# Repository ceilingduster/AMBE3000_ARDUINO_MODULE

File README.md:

# AMBE3000 Arduino Module in KiCad 8
A PCB containing a DVSI AMBE-3000R (or AMBE-3003) Vocoders for use with WebSDRs/Audio transcoding.

This board is based on the design by George Smart, M1GEO and Chris Smart, G8OCV.

The DVSI AMBE parts can be purchased in low volume from the [DVSI Inc. Hardware Product Pricing](https://www.dvsinc.com/products/price.shtml) page. You will need to create a purchase order to buy from DVSI.

# Assembly

The design schematic include details for [JLCPCB](https://jlcpcb.com/) assembly, who assembled mine. You'll likely have to reflow the DVSI AMBE-3000R part yourself, which I did with a PCB reflow hotplate, but you can do any way you wish.

Each schematic component has a [JLCPCB Parts](https://jlcpcb.com/parts)/[LCSC](https://www.lcsc.com/) part number (Cxxxxxx), which can be exported to the BoM using the extra field "LCSC".

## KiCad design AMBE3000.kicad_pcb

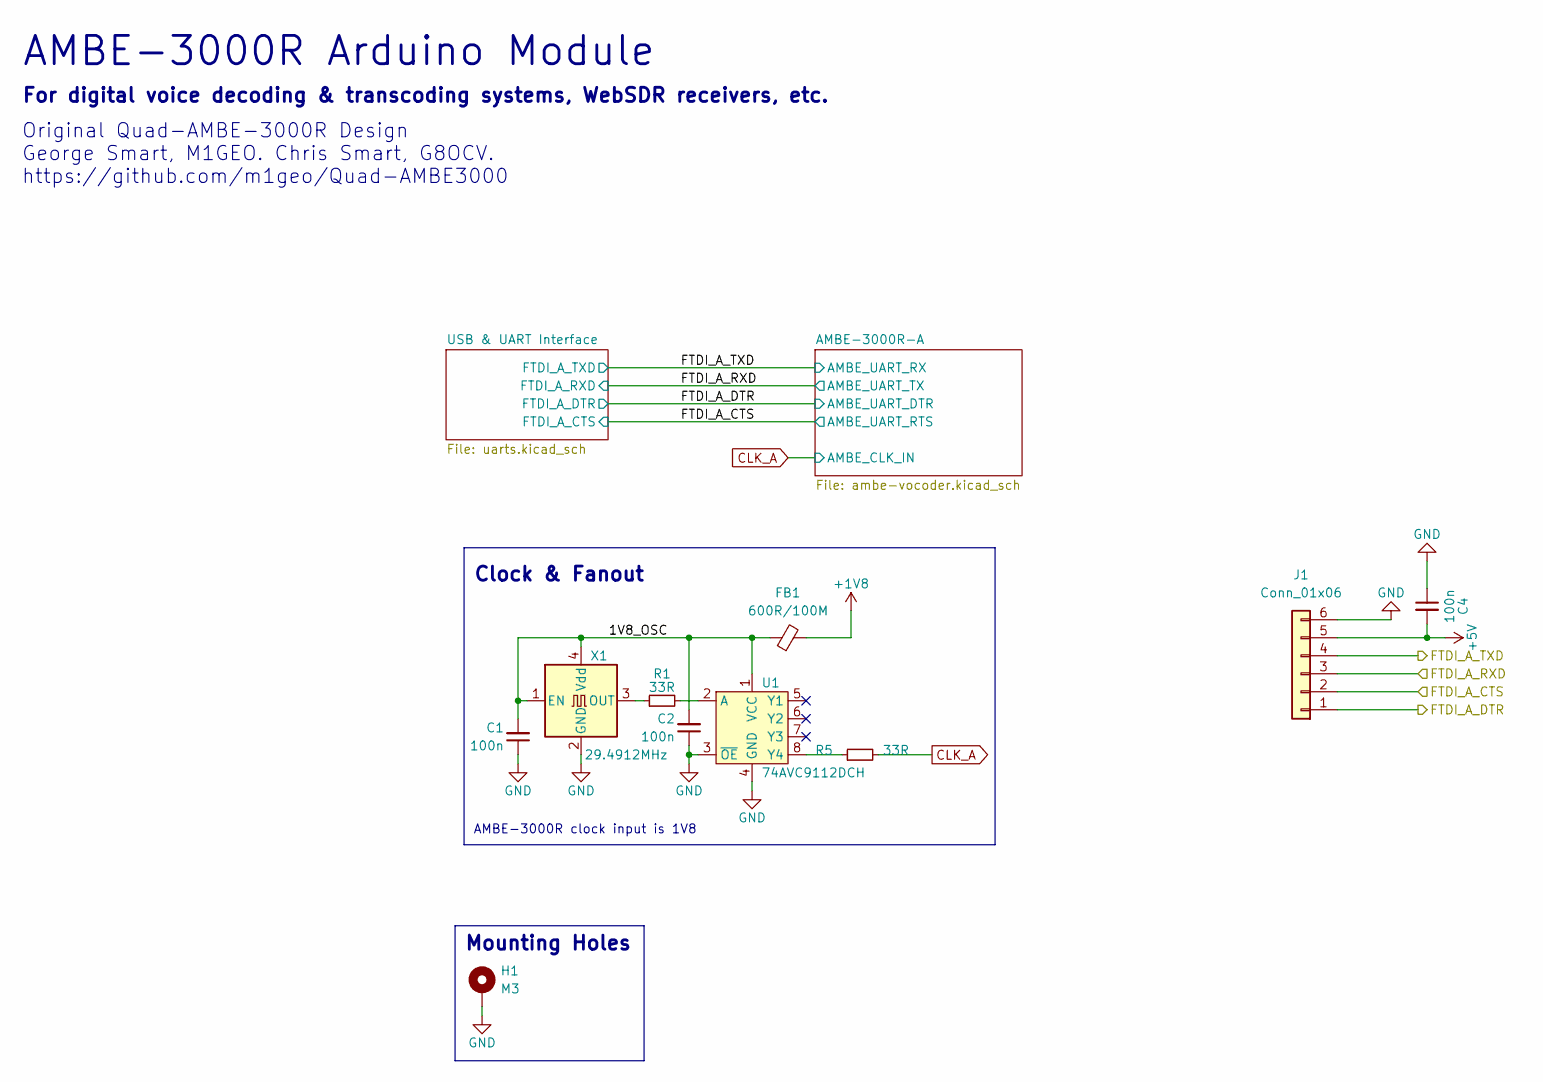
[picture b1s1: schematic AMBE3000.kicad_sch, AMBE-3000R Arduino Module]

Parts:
C1, C2, C4: 100n; C_0603_1608Metric; LCSC C14663
FB1: 600R/100M; L_0805_2012Metric; LCSC C1017
H1: M3; MountingHole_3.2mm_M3_Pad_Via; LCSC DNF
J1: Conn_01x06; PinHeader_1x06_P2.54mm_Vertical
R1, R5: 33R; R_0603_1608Metric; LCSC C23140
U1: 74AVC9112DCH; VSSOP-8_2.4x2.1mm_P0.5mm; LCSC C546283
X1: 29.4912MHz; Oscillator_SMD_Abracon_ASV-4Pin_7.0x5.1mm; LCSC C2901492

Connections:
+1V8: FB1.2; also elsewhere on the board
+5V: C4.2, J1.5; also elsewhere on the board
/1V8_OSC: C1.2, C2.2, FB1.1, U1.1 (VCC), X1.1 (EN), X1.4 (Vdd)
/FTDI_A_CTS: J1.2; also elsewhere on the board
/FTDI_A_DTR: J1.1; also elsewhere on the board
/FTDI_A_RXD: J1.3; also elsewhere on the board
/FTDI_A_TXD: J1.4; also elsewhere on the board
CLK_A: R5.2; also elsewhere on the board
GND: C1.1, C2.1, C4.1, H1.1, J1.6, U1.3 (~OE), U1.4 (GND), X1.2 (GND); also elsewhere on the board
unnamed: R1.2, U1.2 (A)
unnamed: R5.1, U1.8 (Y4)
unnamed: R1.1, X1.3 (OUT)

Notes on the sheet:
Original Quad-AMBE-3000R Design George Smart, M1GEO. Chris Smart, G8OCV. https://github.com/m1geo/Quad-AMBE3000
Mounting Holes
AMBE-3000R Arduino Module
AMBE-3000R clock input is 1V8
For digital voice decoding & transcoding systems, WebSDR receivers, etc.
Clock & Fanout

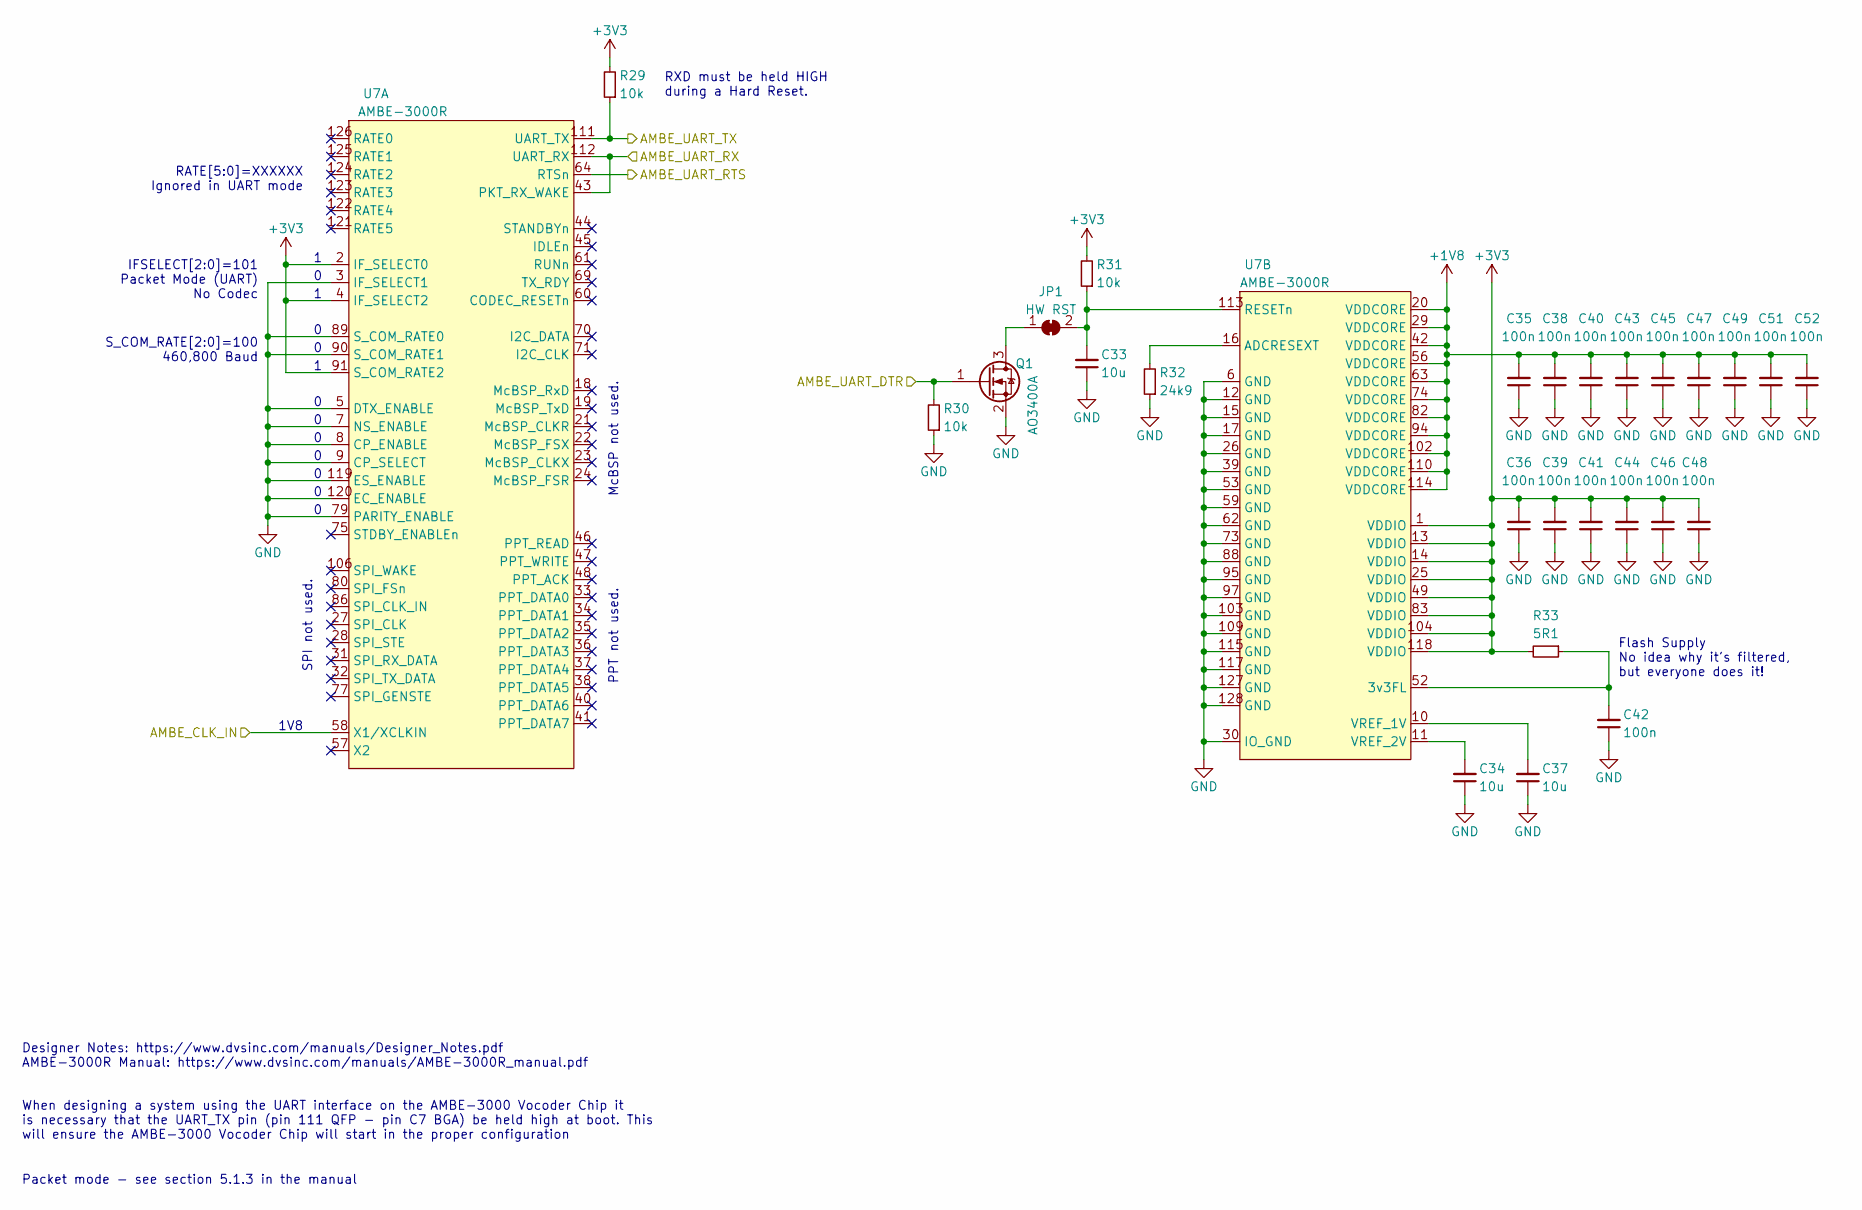
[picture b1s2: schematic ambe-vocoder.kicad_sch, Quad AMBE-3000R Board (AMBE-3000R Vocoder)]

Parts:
C33, C34, C37: 10u; C_0603_1608Metric; LCSC C19702
C35, C36, C38, C39, C40, C41, C42, C43, C44, C45, C46, C47, C48, C49, C51, C52: 100n; C_0603_1608Metric; LCSC C14663
JP1: HW RST; SolderJumper-2_P1.3mm_Open_RoundedPad1.0x1.5mm; LCSC DNF
Q1: AO3400A; SOT-23; LCSC C20917
R29, R30, R31: 10k; R_0603_1608Metric; LCSC C25804
R32: 24k9; R_0603_1608Metric; LCSC C25962
R33: 5R1; R_0603_1608Metric; LCSC C25197
U7: AMBE-3000R; LQFP-128_14x14mm_P0.4mm; LCSC DNF

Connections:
+1V8: C35.2, C38.2, C40.2, C43.2, C45.2, C47.2, C49.2, C51.2, C52.2, U7.20 (VDDCORE), U7.29 (VDDCORE), U7.42 (VDDCORE), U7.56 (VDDCORE), U7.63 (VDDCORE), U7.74 (VDDCORE), U7.82 (VDDCORE), U7.94 (VDDCORE), U7.102 (VDDCORE), U7.110 (VDDCORE), U7.114 (VDDCORE); also elsewhere on the board
+3V3: C36.2, C39.2, C41.2, C44.2, C46.2, C48.2, R29.2, R31.2, R33.2, U7.1 (VDDIO), U7.2 (IF_SELECT0), U7.4 (IF_SELECT2), U7.13 (VDDIO), U7.14 (VDDIO), U7.25 (VDDIO), U7.49 (VDDIO), U7.83 (VDDIO), U7.91 (S_COM_RATE2), U7.104 (VDDIO), U7.118 (VDDIO); also elsewhere on the board
/FTDI_A_CTS: U7.64 (RTSn); also elsewhere on the board
/FTDI_A_DTR: Q1.1 (G), R30.2; also elsewhere on the board
/FTDI_A_RXD: R29.1, U7.111 (UART_TX); also elsewhere on the board
/FTDI_A_TXD: U7.43 (PKT_RX_WAKE), U7.112 (UART_RX); also elsewhere on the board
CLK_A: U7.58 (X1/XCLKIN); also elsewhere on the board
GND: C33.1, C34.1, C35.1, C36.1, C37.1, C38.1, C39.1, C40.1, C41.1, C42.1, C43.1, C44.1, C45.1, C46.1, C47.1, C48.1, C49.1, C51.1, C52.1, Q1.2 (S), R30.1, R32.1, U7.3 (IF_SELECT1), U7.5 (DTX_ENABLE), U7.6 (GND), U7.7 (NS_ENABLE), U7.8 (CP_ENABLE), U7.9 (CP_SELECT), U7.12 (GND), U7.15 (GND), U7.17 (GND), U7.26 (GND), U7.30 (IO_GND), U7.39 (GND), U7.53 (GND), U7.59 (GND), U7.62 (GND), U7.73 (GND), U7.79 (PARITY_ENABLE), U7.88 (GND), U7.89 (S_COM_RATE0), U7.90 (S_COM_RATE1), U7.95 (GND), U7.97 (GND), U7.103 (GND), U7.109 (GND), U7.115 (GND), U7.117 (GND), U7.119 (ES_ENABLE), U7.120 (EC_ENABLE), U7.127 (GND), U7.128 (GND); also elsewhere on the board
unnamed: JP1.1 (A), Q1.3 (D)
unnamed: C33.2, JP1.2 (B), R31.1, U7.113 (RESETn)
unnamed: C42.2, R33.1, U7.52 (3v3FL)
unnamed: R32.2, U7.16 (ADCRESEXT)
unnamed: C37.2, U7.10 (VREF_1V)
unnamed: C34.2, U7.11 (VREF_2V)

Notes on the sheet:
1V8
IFSELECT[2:0]=101 Packet Mode (UART) No Codec
McBSP not used.
RATE[5:0]=XXXXXX Ignored in UART mode
Packet mode - see section 5.1.3 in the manual
Designer Notes: https://www.dvsinc.com/manuals/Designer_Notes.pdf AMBE-3000R Manual: https://www.dvsinc.com/manuals/AMBE-3000R_manual.pdf
S_COM_RATE[2:0]=100 460,800 Baud
PPT not used.
Flash Supply No idea why it's filtered, but everyone does it!
SPI not used.
RXD must be held HIGH during a Hard Reset.
When designing a system using the UART interface on the AMBE-3000 Vocoder Chip it is necessary that the UART_TX pin (pin 111 QFP - pin C7 BGA) be held high at boot. This will ensure the AMBE-3000 Vocoder Chip will start in the proper configuration

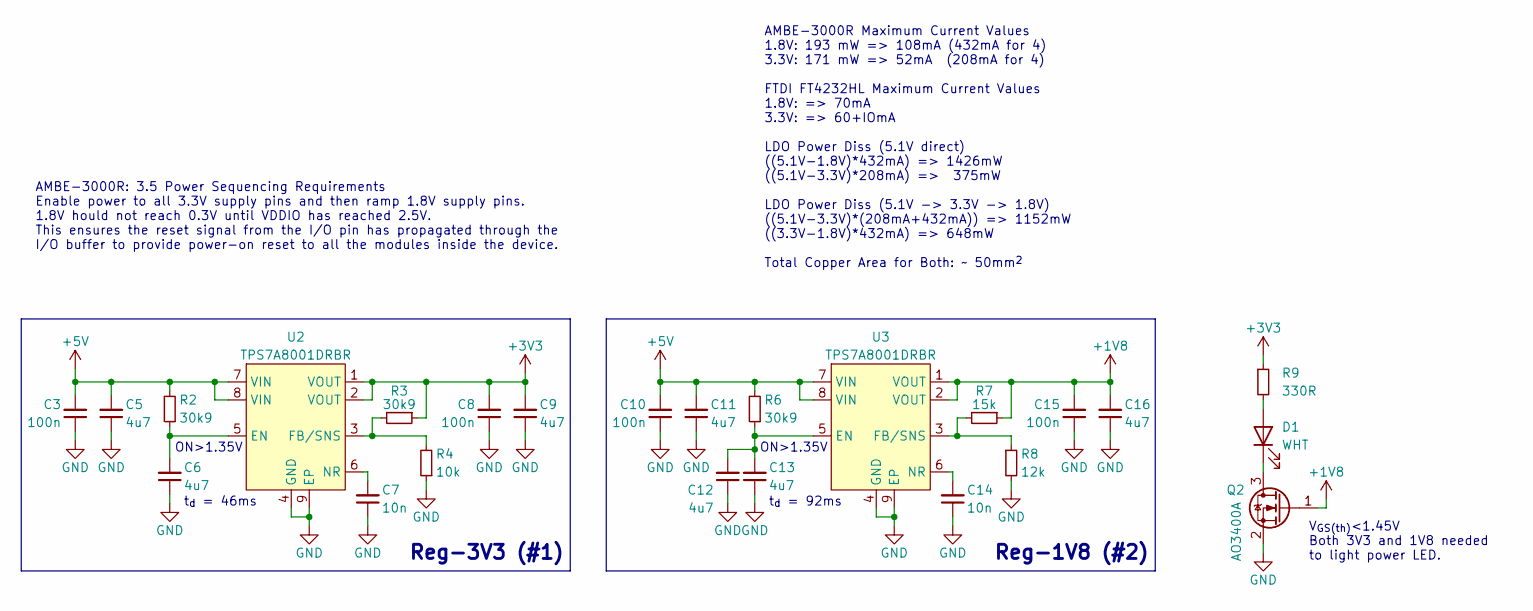
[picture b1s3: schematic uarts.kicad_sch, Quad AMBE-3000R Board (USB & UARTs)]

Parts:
C3, C8, C10, C15: 100n; C_0603_1608Metric; LCSC C14663
C5, C6, C9, C11, C12, C13, C16: 4u7; C_0603_1608Metric; LCSC C19666
C7, C14: 10n; C_0603_1608Metric; LCSC C57112
D1: WHT; LED_0603_1608Metric; LCSC C2290
Q2: AO3400A; SOT-23; LCSC C20917
R2, R3, R6: 30k9; R_0603_1608Metric; LCSC C217957
R4: 10k; R_0603_1608Metric; LCSC C25804
R7: 15k; R_0603_1608Metric; LCSC C22809
R8: 12k; R_0603_1608Metric; LCSC C22790
R9: 330R; R_0603_1608Metric; LCSC C23138
U2, U3: TPS7A8001DRBR; Texas_DRB0008A; LCSC C105265

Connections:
+1V8: C15.2, C16.2, Q2.1 (G), R7.1, U3.1 (VOUT), U3.2 (VOUT); also elsewhere on the board
+3V3: C8.2, C9.2, R3.1, R9.1, U2.1 (VOUT), U2.2 (VOUT); also elsewhere on the board
+5V: C3.2, C5.2, C10.2, C11.2, R2.2, R6.2, U2.7 (VIN), U2.8 (VIN), U3.7 (VIN), U3.8 (VIN); also elsewhere on the board
GND: C3.1, C5.1, C6.1, C7.1, C8.1, C9.1, C10.1, C11.1, C12.1, C13.1, C14.1, C15.1, C16.1, Q2.2 (S), R4.1, R8.2, U2.4 (GND), U2.9 (EP), U3.4 (GND), U3.9 (EP); also elsewhere on the board
unnamed: D1.2 (A), R9.2
unnamed: D1.1 (K), Q2.3 (D)
unnamed: C6.2, R2.1, U2.5 (EN)
unnamed: R3.2, R4.2, U2.3 (FB/SNS)
unnamed: C7.2, U2.6 (NR)
unnamed: C12.2, C13.2, R6.1, U3.5 (EN)
unnamed: R7.2, R8.1, U3.3 (FB/SNS)
unnamed: C14.2, U3.6 (NR)

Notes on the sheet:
Reg-1V8 (#2)
V_{GS(th)}<1.45V Both 3V3 and 1V8 needed to light power LED.
ON>1.35V
t_{d} = 92ms
Reg-3V3 (#1)
AMBE-3000R Maximum Current Values 1.8V: 193 mW => 108mA (432mA for 4) 3.3V: 171 mW => 52mA (208mA for 4) FTDI FT4232HL Maximum Current Values 1.8V: => 70mA 3.3V: => 60+IOmA LDO Power Diss (5.1V direct) ((5.1V-1.8V)*432mA) => 1426mW ((5.1V-3.3V)*208mA) => 375mW LDO Power Diss (5.1V -> 3.3V -> 1.8V) 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
t_{d} = 46ms
AMBE-3000R: 3.5 Power Sequencing Requirements Enable power to all 3.3V supply pins and then ramp 1.8V supply pins. 1.8V hould not reach 0.3V until VDDIO has reached 2.5V. This ensures the reset signal from the I/O pin has propagated through the I/O buffer to provide power-on reset to all the module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

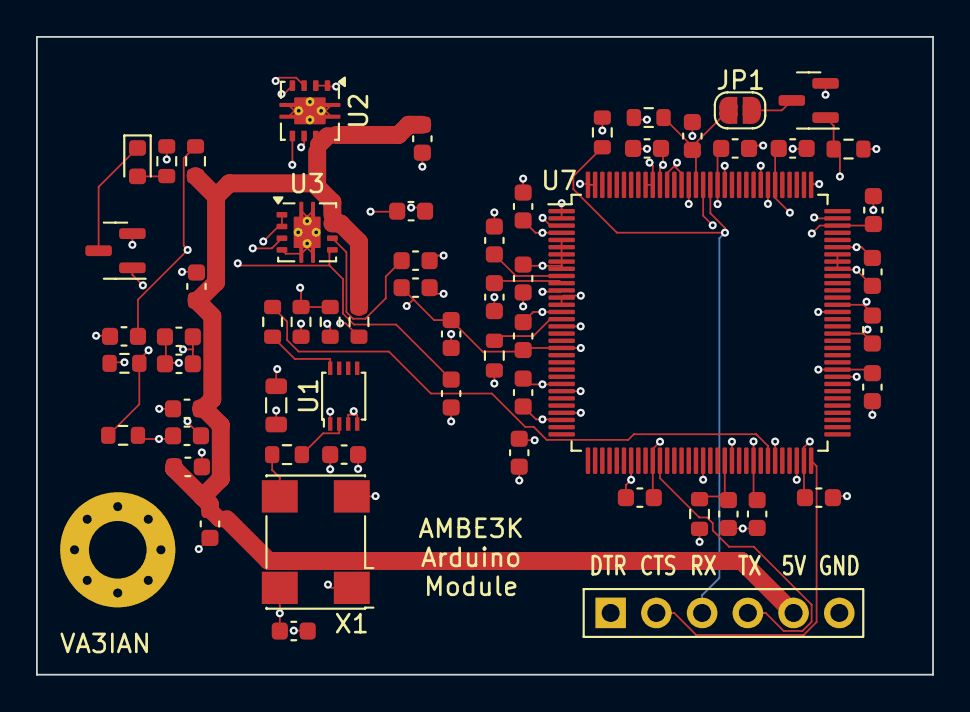
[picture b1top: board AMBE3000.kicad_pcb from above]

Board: 4 copper layers, 49.8 x 35.4 mm, 61 parts (0 on the bottom side), 27 nets.

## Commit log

2024-04-21 Initial Draft v0.1
